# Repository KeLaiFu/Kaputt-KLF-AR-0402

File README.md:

Rework of Kaputtpanzers 6HP eurorack AR module. My version shaves off 2HP and combines the originals LED and button into one unit. 
This version uses 0402 components and is very cheap to get assembled at jlcpcb as all the parts are from the basic component range. 

note* I havn't use the exact assembly files posted here, so double check them if you intend to use them.
It's not really suited for hand soldering due to the tiny pitch of 0402.

Panel should be fabricated in FR4 due to the illuminated logo.

Module is fully tested and working, No further revision are planned.

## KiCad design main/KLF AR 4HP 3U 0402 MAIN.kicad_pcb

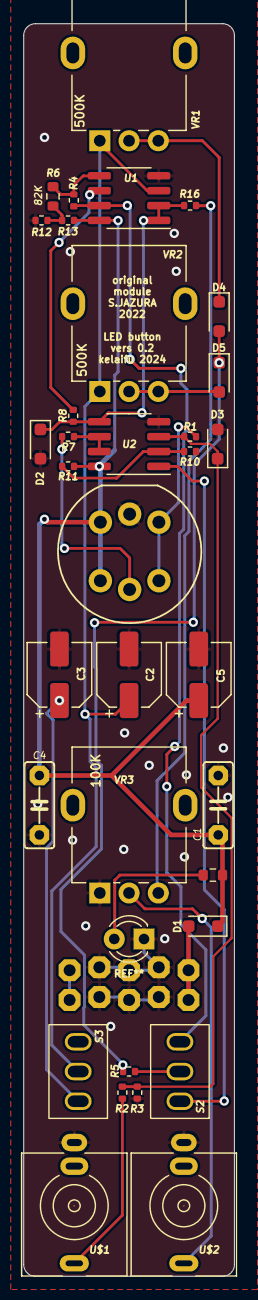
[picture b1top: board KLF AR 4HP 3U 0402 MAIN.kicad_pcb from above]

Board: 2 copper layers, 18.0 x 107.0 mm, 33 parts (1 on the bottom side), 22 nets.

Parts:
C1, C4: 100N; 000_7,5MM_FOIL_STANDARD
C2: 2U2; CP_Elec_5x5.4
C3, C5: 10U; CP_Elec_5x5.4
D1: 5817; D_SOD-323_HandSoldering
D2, D3: bat85; D_SOD-323_HandSoldering
D4, D5: 4148; D_SOD-323_HandSoldering
R1, R4, R11: 22K; R_0402_1005Metric
R2, R12, R13: 10K; R_0402_1005Metric
R3: 100k; R_0402_1005Metric
R5: 220R; R_0402_1005Metric
R6: 82K; R_0603_1608Metric
R7, R16: 4K7; R_0402_1005Metric
R8: 100K; R_0402_1005Metric
R10: 2K2; R_0402_1005Metric
S2: LOOP; sm_SPDT_rec_lug.2
S3: TIME; sm_SPDT_rec_lug.2
SV1: POWER; EURO_PWR_HEADER_LOCK
U1, U2: LM358; SOP-8_3.76x4.96mm_P1.27mm
U$1: GATE; thonkiconn_offset
U$2: OUT; thonkiconn_offset
VR1, VR2: 500K; Potentiometer_Alpha_RD901F-40-00D_Single_Vertical_centered
VR3: 100K; Potentiometer_Alpha_RD901F-40-00D_Single_Vertical_centered

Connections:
GND: C1.2, C2.2, C3.2, C4.2, C5.2, D2.2, D3.2, R3.1, R10.1, R12.1, SV1.GND1, SV1.GND2, SV1.GND3, SV1.GND4, SV1.GND5, SV1.GND6, U1.4, U2.4, U$1.GND, U$2.GND, VR3.1
unnamed: D1.2, SV1.POS1, SV1.POS2
unnamed: SV1.NEG1, SV1.NEG2
unnamed: U$2.P$1, VR3.2
unnamed: R16.2, VR3.3
unnamed: R7.2, U2.6, U2.7
unnamed: D3.1, R1.1, R2.2, R3.2, U2.3
unnamed: R2.1, U$1.P$1
unnamed: S2.1, U2.1
unnamed: R4.1, S2.3, U1.7
unnamed: R5.1, S2.2
unnamed: D4.1, VR1.2, VR1.3
unnamed: D4.2, D5.1, R5.2
unnamed: D5.2, VR2.2, VR2.3
unnamed: C3.1, S3.1
unnamed: C2.1, S3.2, U1.3, VR1.1, VR2.1
unnamed: R4.2, R6.1, U1.5
unnamed: R8.2, U1.6
unnamed: D2.1, R8.1, R16.1, U1.1, U1.2, U2.5
VCC: C1.1, C4.1, C5.1, D1.1, R11.2, R13.2, U1.8, U2.8
VCOMP: R10.2, R11.1, U2.2
VREF: R6.2, R12.2, R13.1

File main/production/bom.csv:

Designator,Footprint,Quantity,Value,LCSC Part #
"C1, C4","000_7,5MM_FOIL_STANDARD",2,100N,
C2,CP_Elec_5x5.4,1,2U2,
"C3, C5",CP_Elec_5x5.4,2,10U,
D1,D_SOD-323_HandSoldering,1,5817,
"D2, D3",D_SOD-323_HandSoldering,2,bat85,
"D4, D5",D_SOD-323_HandSoldering,2,4148,
"R1, R11, R4",0402,3,22K,
R10,0402,1,2K2,
"R12, R13, R2",0402,3,10K,
"R16, R7",0402,2,4K7,
"R3, R8",0402,2,100k,
R5,0402,1,220R,
R6,0603,1,82K,
S2,sm_SPDT_rec_lug.2,1,LOOP,
S3,sm_SPDT_rec_lug.2,1,TIME,
SV1,EURO_PWR_HEADER_LOCK,1,POWER,
U$1,thonkiconn_offset,1,GATE,
U$2,thonkiconn_offset,1,OUT,
"U1, U2",SOP-8_3.76x4.96mm_P1.27mm,2,LM358,
"VR1, VR2",Potentiometer_Alpha_RD901F-40-00D_Single_Vertical_centered,2,500K,
VR3,Potentiometer_Alpha_RD901F-40-00D_Single_Vertical_centered,1,100K,

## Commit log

2025-06-30 Rework of kaputtpanzers AR module.
    Rework of a eurorack module kindly shared by Kapputtpanzer on modwiggler.
    My version combines the LED and button into a single flashing button and shrinks it down from 6HP to 4HP.
